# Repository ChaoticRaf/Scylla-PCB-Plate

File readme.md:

# Fork of the original Scylla PCB

My goal is to adapt the pcb of the main part and the thumbclusters to use hotswap sockets. In particular I plan to use Kailh MX Hotswap sockets with salvaged MX Blues. They are not clear so the per key RGB wont work, but I will keep the option open as I go forward.
I will try to post updates and pictures of the progress once I order the parts.

# Scylla PCB - plate

Flexible PCB made for the Scylla.

With per-key RGB.

This repository contains all files necessary to order a PCB.

If you want to modify the design files, the Kicad sources are included.
<!-- If you just want to order the PCBs, check out the Release section which contain the gerber files. -->

## How to order
Order with a 0.6mm or 0.8mm PCB thickness

# Support the original creator on Patreon
If you like the keyboard, please consider helping bastardkb on Patreon: https://www.patreon.com/bastardkb

## License
Licensed under CC BY-NC-SA 4.0
Copyright Quentin Lebastard 2021

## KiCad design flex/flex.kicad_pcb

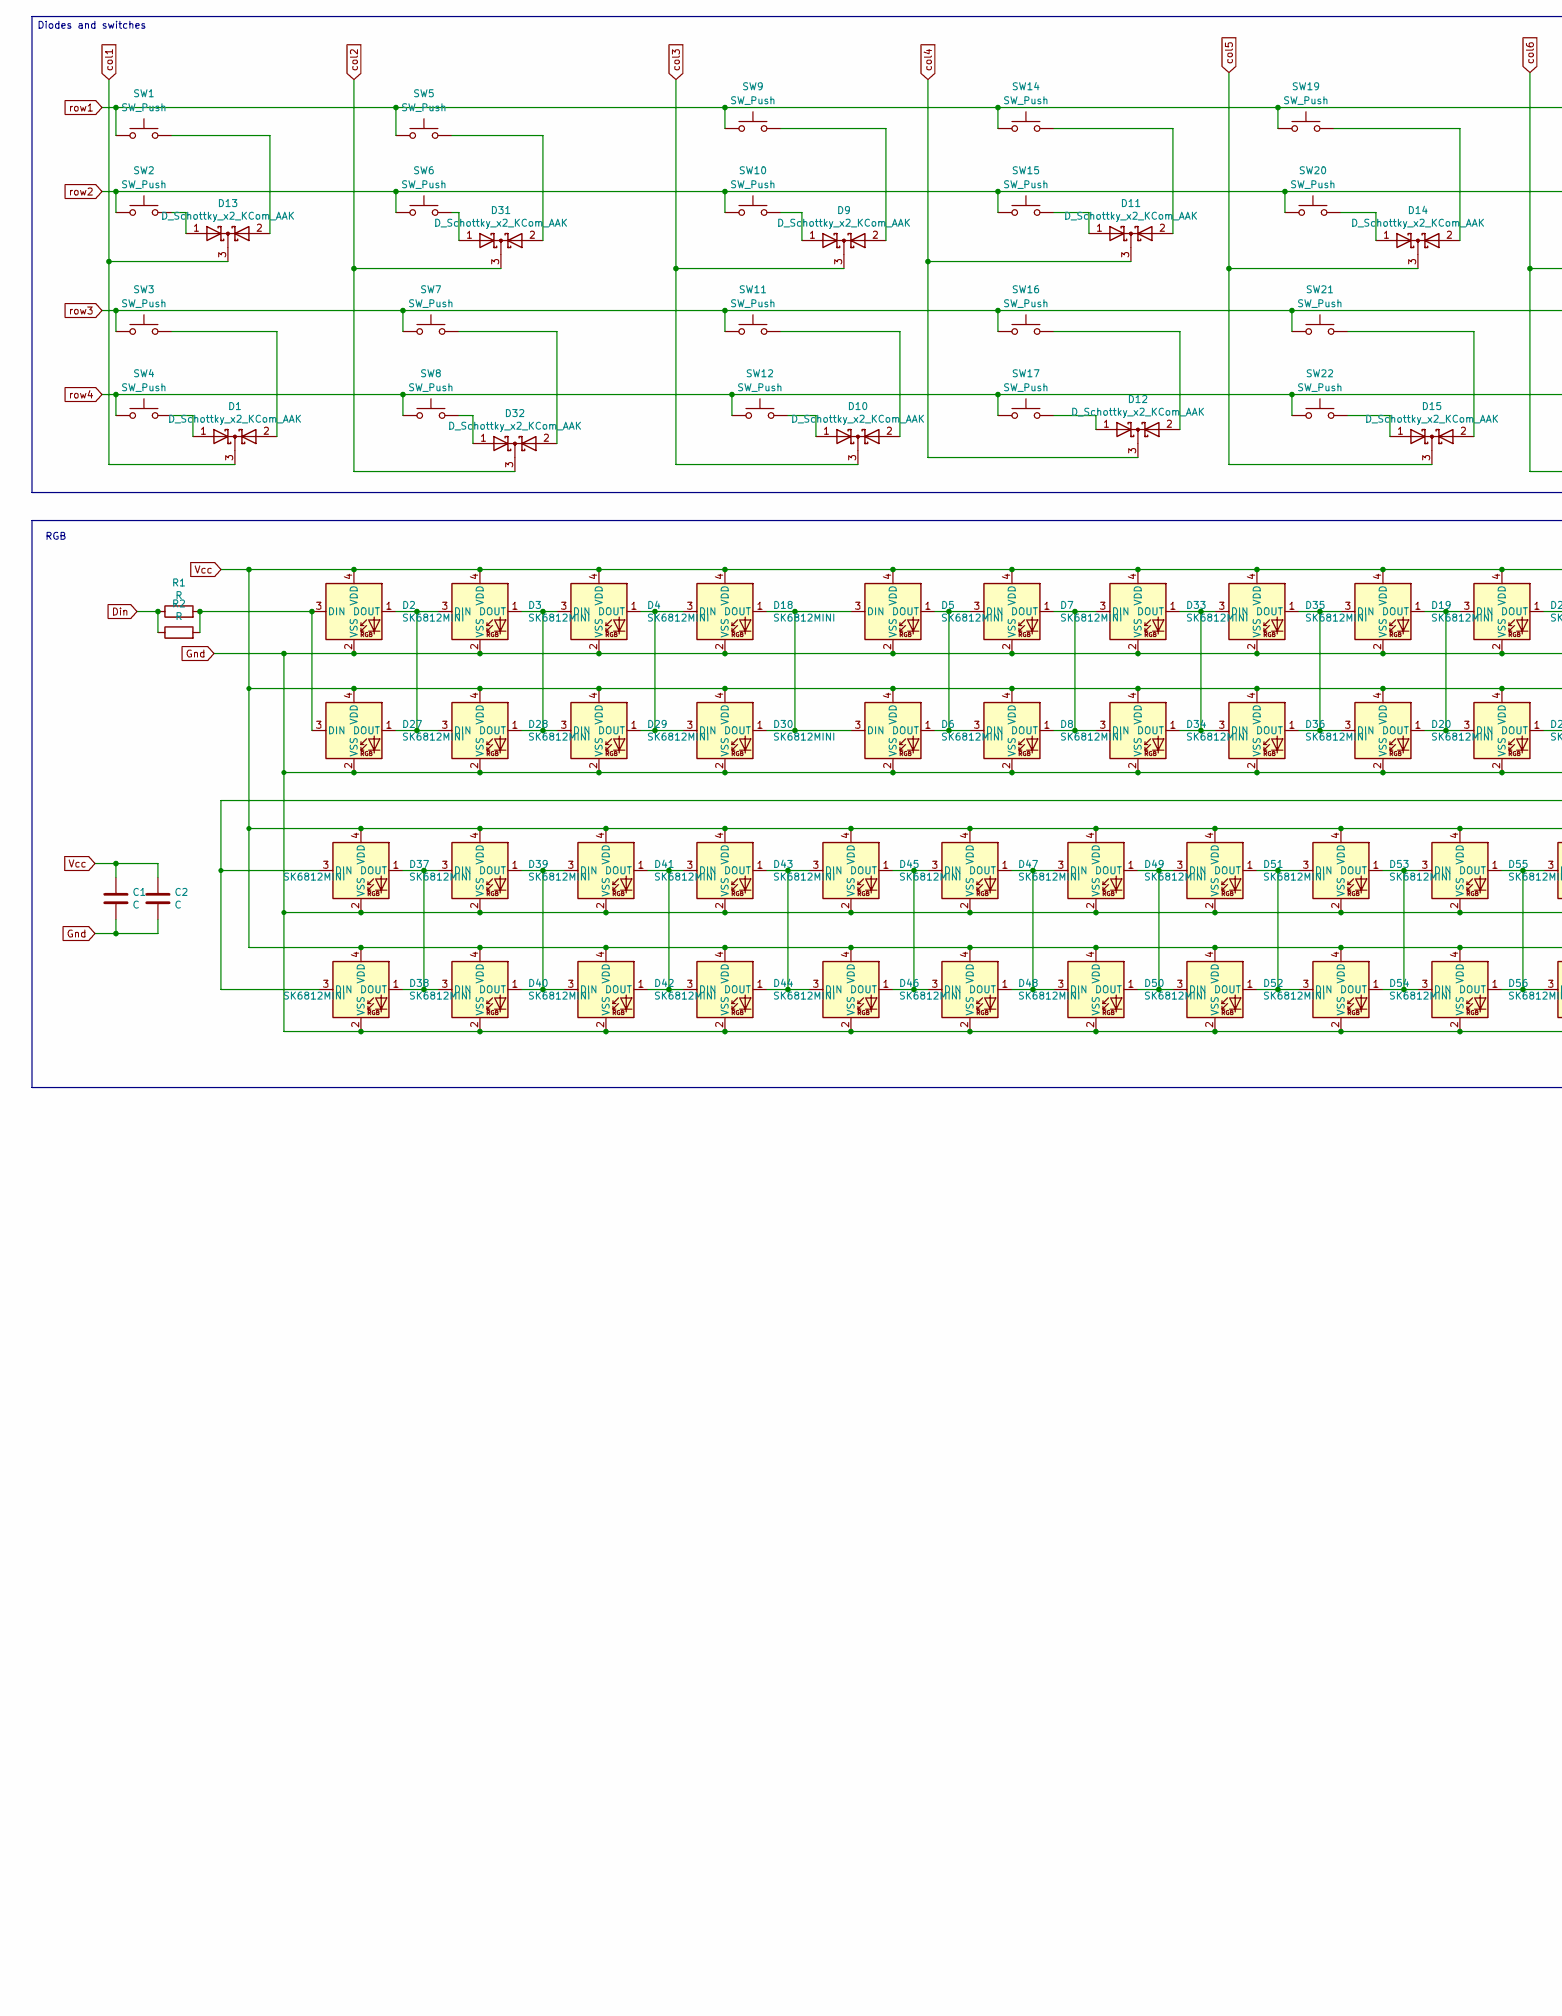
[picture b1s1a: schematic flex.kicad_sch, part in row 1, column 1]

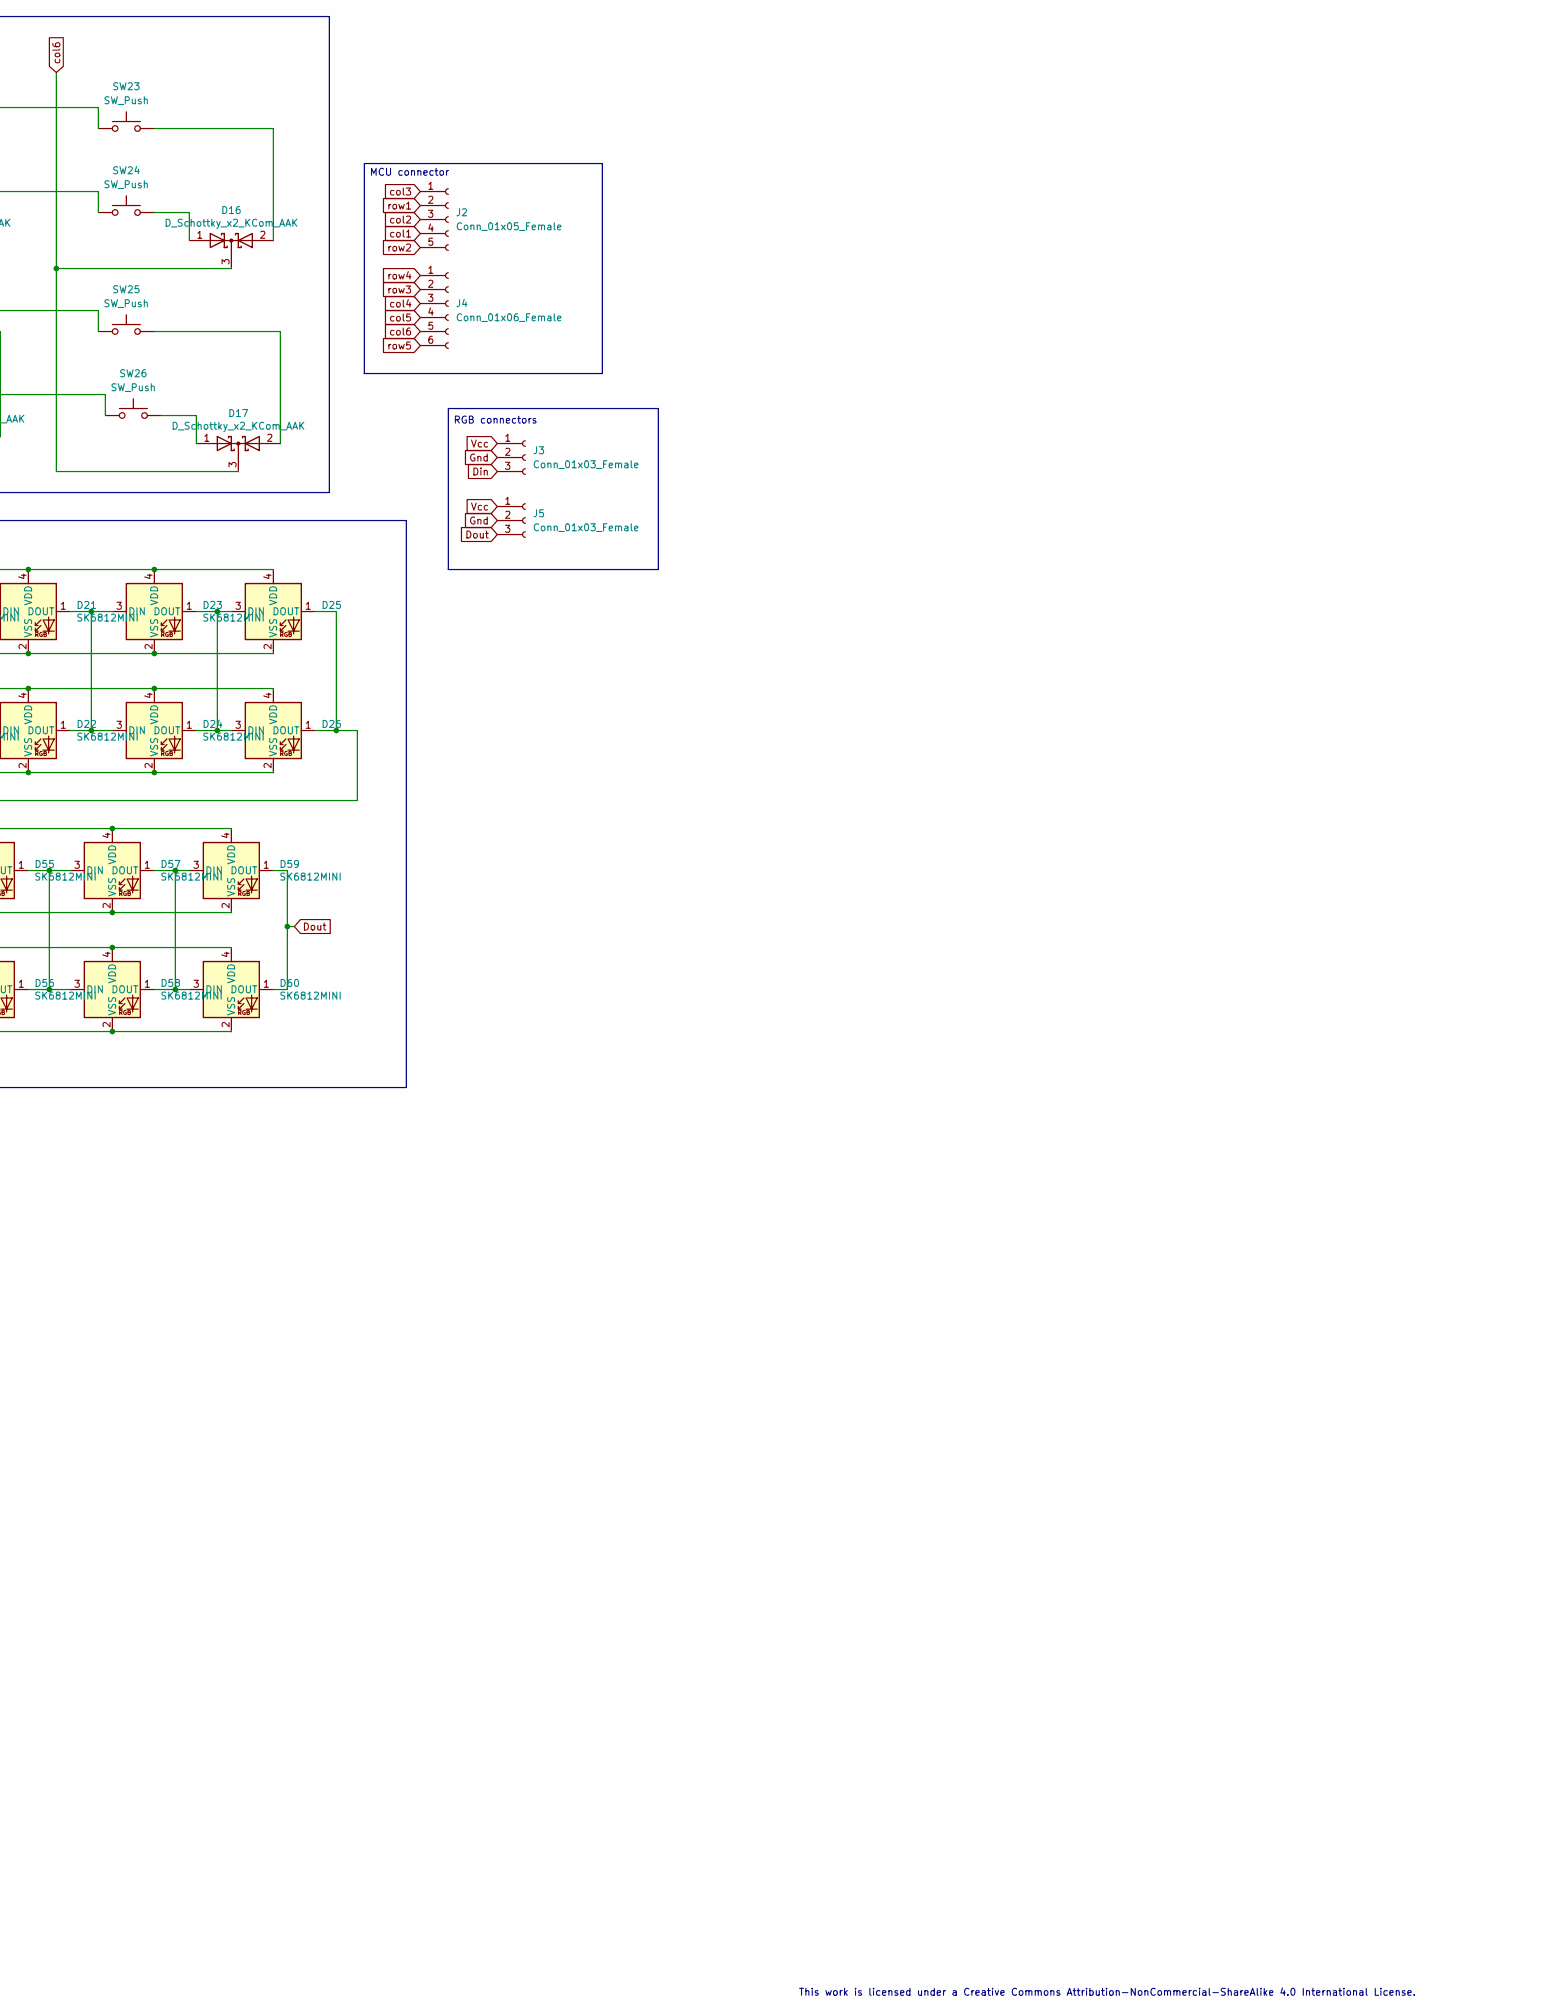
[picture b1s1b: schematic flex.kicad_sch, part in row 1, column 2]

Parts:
C1, C2: C; C_1206_3216Metric_Pad1.42x1.75mm_HandSolder
D1, D9, D10, D11, D12, D13, D14, D15, D16, D17, D31, D32: D_Schottky_x2_KCom_AAK; TSOT-23_HandSoldering
D2, D3, D4, D5, D7, D18, D19, D21, D23, D25, D33, D35, D37, D39, D41, D43, D45, D47, D49, D51, D53, D55, D57, D59: SK6812MINI; YS-SK6812MINI-E_REVERSE
D6, D8, D20, D22, D24, D26, D27, D28, D29, D30, D34, D36, D38, D40, D42, D44, D46, D48, D50, D52, D54, D56, D58, D60: SK6812MINI; YS-SK6812MINI-E_REVERSE_NO_EDGECUT
J2: Conn_01x05_Female; PinHeader_1x05_P2.54mm_Vertical
J3, J5: Conn_01x03_Female; PinHeader_1x03_P2.54mm_Vertical
J4: Conn_01x06_Female; PinHeader_1x06_P2.54mm_Vertical
R1, R2: R; R_1206_3216Metric_Pad1.42x1.75mm_HandSolder
SW1, SW2, SW3, SW4, SW5, SW6, SW7, SW8, SW9, SW10, SW11, SW12, SW14, SW15, SW16, SW17, SW19, SW20, SW21, SW22, SW23, SW24, SW25, SW26: SW_Push; Kailh_socket_MX_flippable

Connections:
Din: J3.3, R1.1, R2.1
Dout: D59.1 (DOUT), D60.1 (DOUT), J5.3
Gnd: C1.2, C2.2, D2.2 (VSS), D3.2 (VSS), D4.2 (VSS), D5.2 (VSS), D6.2 (VSS), D7.2 (VSS), D8.2 (VSS), D18.2 (VSS), D19.2 (VSS), D20.2 (VSS), D21.2 (VSS), D22.2 (VSS), D23.2 (VSS), D24.2 (VSS), D25.2 (VSS), D26.2 (VSS), D27.2 (VSS), D28.2 (VSS), D29.2 (VSS), D30.2 (VSS), D33.2 (VSS), D34.2 (VSS), D35.2 (VSS), D36.2 (VSS), D37.2 (VSS), D38.2 (VSS), D39.2 (VSS), D40.2 (VSS), D41.2 (VSS), D42.2 (VSS), D43.2 (VSS), D44.2 (VSS), D45.2 (VSS), D46.2 (VSS), D47.2 (VSS), D48.2 (VSS), D49.2 (VSS), D50.2 (VSS), D51.2 (VSS), D52.2 (VSS), D53.2 (VSS), D54.2 (VSS), D55.2 (VSS), D56.2 (VSS), D57.2 (VSS), D58.2 (VSS), D59.2 (VSS), D60.2 (VSS), J3.2, J5.2
unnamed: D1.1 (A), SW4.2
unnamed: D1.2 (A), SW3.2
unnamed: D2.1 (DOUT), D3.3 (DIN), D27.1 (DOUT), D28.3 (DIN)
unnamed: D2.3 (DIN), D27.3 (DIN), R1.2, R2.2
unnamed: D5.1 (DOUT), D6.1 (DOUT), D7.3 (DIN), D8.3 (DIN)
unnamed: D9.1 (A), SW10.2
unnamed: D9.2 (A), SW9.2
unnamed: D10.1 (A), SW12.2
unnamed: D10.2 (A), SW11.2
unnamed: D11.1 (A), SW15.2
unnamed: D11.2 (A), SW14.2
unnamed: D12.1 (A), SW17.2
unnamed: D12.2 (A), SW16.2
unnamed: D13.1 (A), SW2.2
unnamed: D13.2 (A), SW1.2
unnamed: D14.1 (A), SW20.2
unnamed: D14.2 (A), SW19.2
unnamed: D15.1 (A), SW22.2
unnamed: D15.2 (A), SW21.2
unnamed: D16.1 (A), SW24.2
unnamed: D16.2 (A), SW23.2
unnamed: D17.1 (A), SW26.2
unnamed: D17.2 (A), SW25.2
unnamed: D5.3 (DIN), D6.3 (DIN), D18.1 (DOUT), D30.1 (DOUT)
unnamed: D4.1 (DOUT), D18.3 (DIN), D29.1 (DOUT), D30.3 (DIN)
unnamed: D19.1 (DOUT), D20.1 (DOUT), D21.3 (DIN), D22.3 (DIN)
unnamed: D19.3 (DIN), D20.3 (DIN), D35.1 (DOUT), D36.1 (DOUT)
unnamed: D21.1 (DOUT), D22.1 (DOUT), D23.3 (DIN), D24.3 (DIN)
unnamed: D23.1 (DOUT), D24.1 (DOUT), D25.3 (DIN), D26.3 (DIN)
unnamed: D25.1 (DOUT), D26.1 (DOUT), D37.3 (DIN), D38.3 (DIN)
unnamed: D3.1 (DOUT), D4.3 (DIN), D28.1 (DOUT), D29.3 (DIN)
unnamed: D31.1 (A), SW6.2
unnamed: D31.2 (A), SW5.2
unnamed: D32.1 (A), SW8.2
unnamed: D32.2 (A), SW7.2
unnamed: D33.1 (DOUT), D34.1 (DOUT), D35.3 (DIN), D36.3 (DIN)
unnamed: D7.1 (DOUT), D8.1 (DOUT), D33.3 (DIN), D34.3 (DIN)
unnamed: D37.1 (DOUT), D38.1 (DOUT), D39.3 (DIN), D40.3 (DIN)
unnamed: D39.1 (DOUT), D40.1 (DOUT), D41.3 (DIN), D42.3 (DIN)
unnamed: D41.1 (DOUT), D42.1 (DOUT), D43.3 (DIN), D44.3 (DIN)
unnamed: D43.1 (DOUT), D44.1 (DOUT), D45.3 (DIN), D46.3 (DIN)
unnamed: D45.1 (DOUT), D46.1 (DOUT), D47.3 (DIN), D48.3 (DIN)
unnamed: D47.1 (DOUT), D48.1 (DOUT), D49.3 (DIN), D50.3 (DIN)
unnamed: D49.1 (DOUT), D50.1 (DOUT), D51.3 (DIN), D52.3 (DIN)
unnamed: D51.1 (DOUT), D52.1 (DOUT), D53.3 (DIN), D54.3 (DIN)
unnamed: D53.1 (DOUT), D54.1 (DOUT), D55.3 (DIN), D56.3 (DIN)
unnamed: D55.1 (DOUT), D56.1 (DOUT), D57.3 (DIN), D58.3 (DIN)
unnamed: D57.1 (DOUT), D58.1 (DOUT), D59.3 (DIN), D60.3 (DIN)
Vcc: C1.1, C2.1, D2.4 (VDD), D3.4 (VDD), D4.4 (VDD), D5.4 (VDD), D6.4 (VDD), D7.4 (VDD), D8.4 (VDD), D18.4 (VDD), D19.4 (VDD), D20.4 (VDD), D21.4 (VDD), D22.4 (VDD), D23.4 (VDD), D24.4 (VDD), D25.4 (VDD), D26.4 (VDD), D27.4 (VDD), D28.4 (VDD), D29.4 (VDD), D30.4 (VDD), D33.4 (VDD), D34.4 (VDD), D35.4 (VDD), D36.4 (VDD), D37.4 (VDD), D38.4 (VDD), D39.4 (VDD), D40.4 (VDD), D41.4 (VDD), D42.4 (VDD), D43.4 (VDD), D44.4 (VDD), D45.4 (VDD), D46.4 (VDD), D47.4 (VDD), D48.4 (VDD), D49.4 (VDD), D50.4 (VDD), D51.4 (VDD), D52.4 (VDD), D53.4 (VDD), D54.4 (VDD), D55.4 (VDD), D56.4 (VDD), D57.4 (VDD), D58.4 (VDD), D59.4 (VDD), D60.4 (VDD), J3.1, J5.1
col1: D1.3 (K), D13.3 (K), J2.4
col2: D31.3 (K), D32.3 (K), J2.3
col3: D9.3 (K), D10.3 (K), J2.1
col4: D11.3 (K), D12.3 (K), J4.3
col5: D14.3 (K), D15.3 (K), J4.4
col6: D16.3 (K), D17.3 (K), J4.5
row1: J2.2, SW1.1, SW5.1, SW9.1, SW14.1, SW19.1, SW23.1
row2: J2.5, SW2.1, SW6.1, SW10.1, SW15.1, SW20.1, SW24.1
row3: J4.2, SW3.1, SW7.1, SW11.1, SW16.1, SW21.1, SW25.1
row4: J4.1, SW4.1, SW8.1, SW12.1, SW17.1, SW22.1, SW26.1
row5: J4.6

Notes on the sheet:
Diodes and switches
RGB
MCU connector
This work is licensed under a Creative Commons Attribution-NonCommercial-ShareAlike 4.0 International License.
RGB connectors

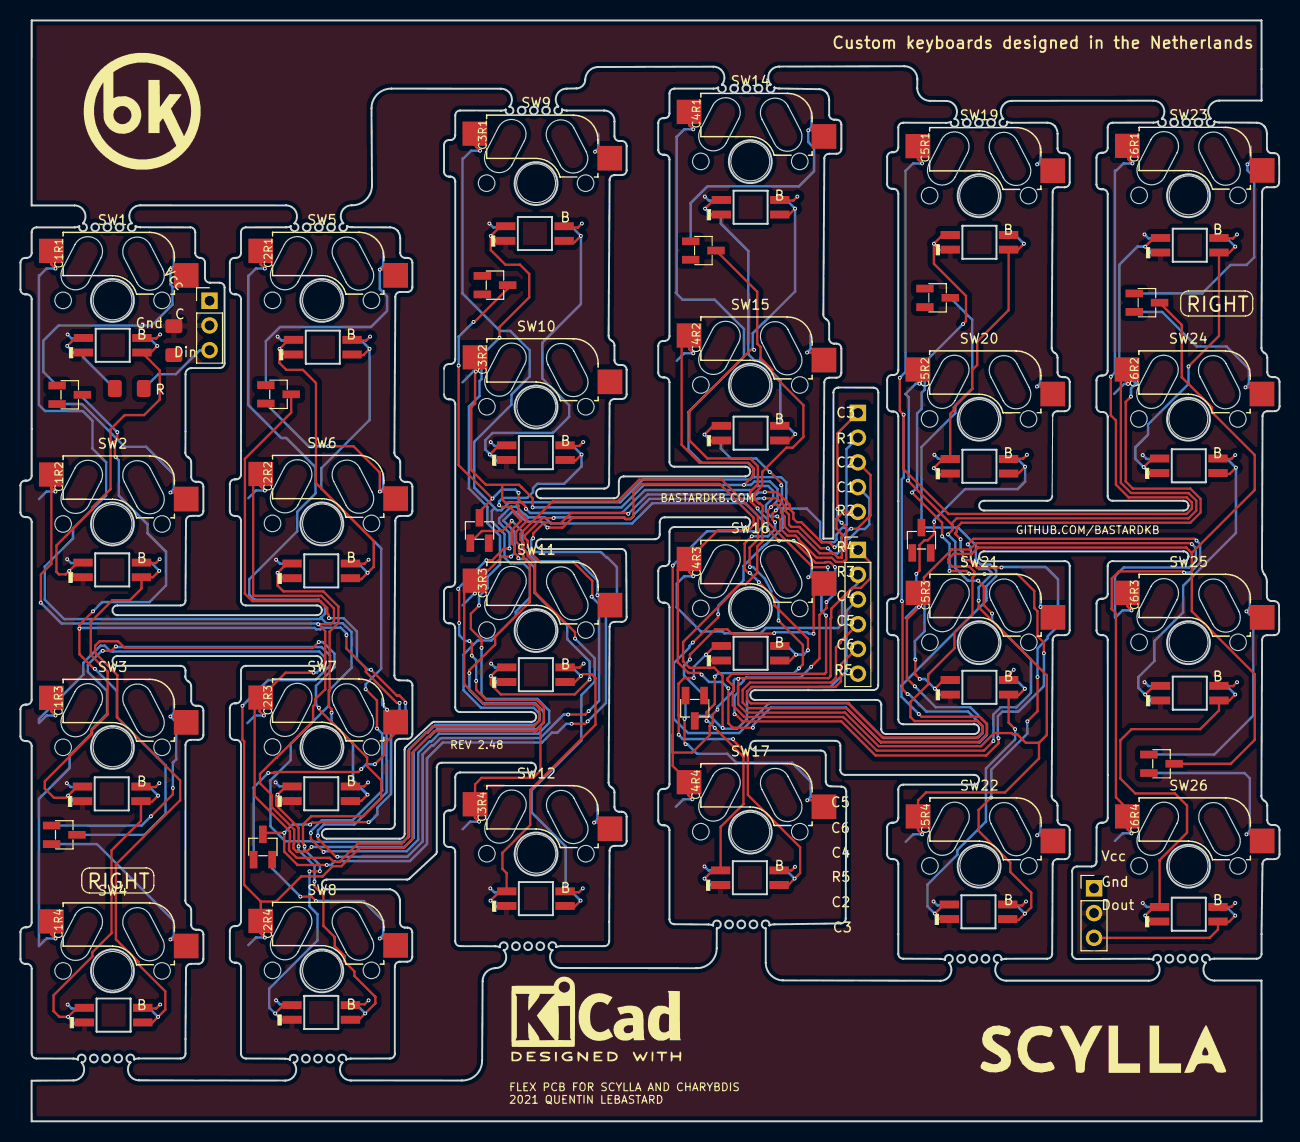
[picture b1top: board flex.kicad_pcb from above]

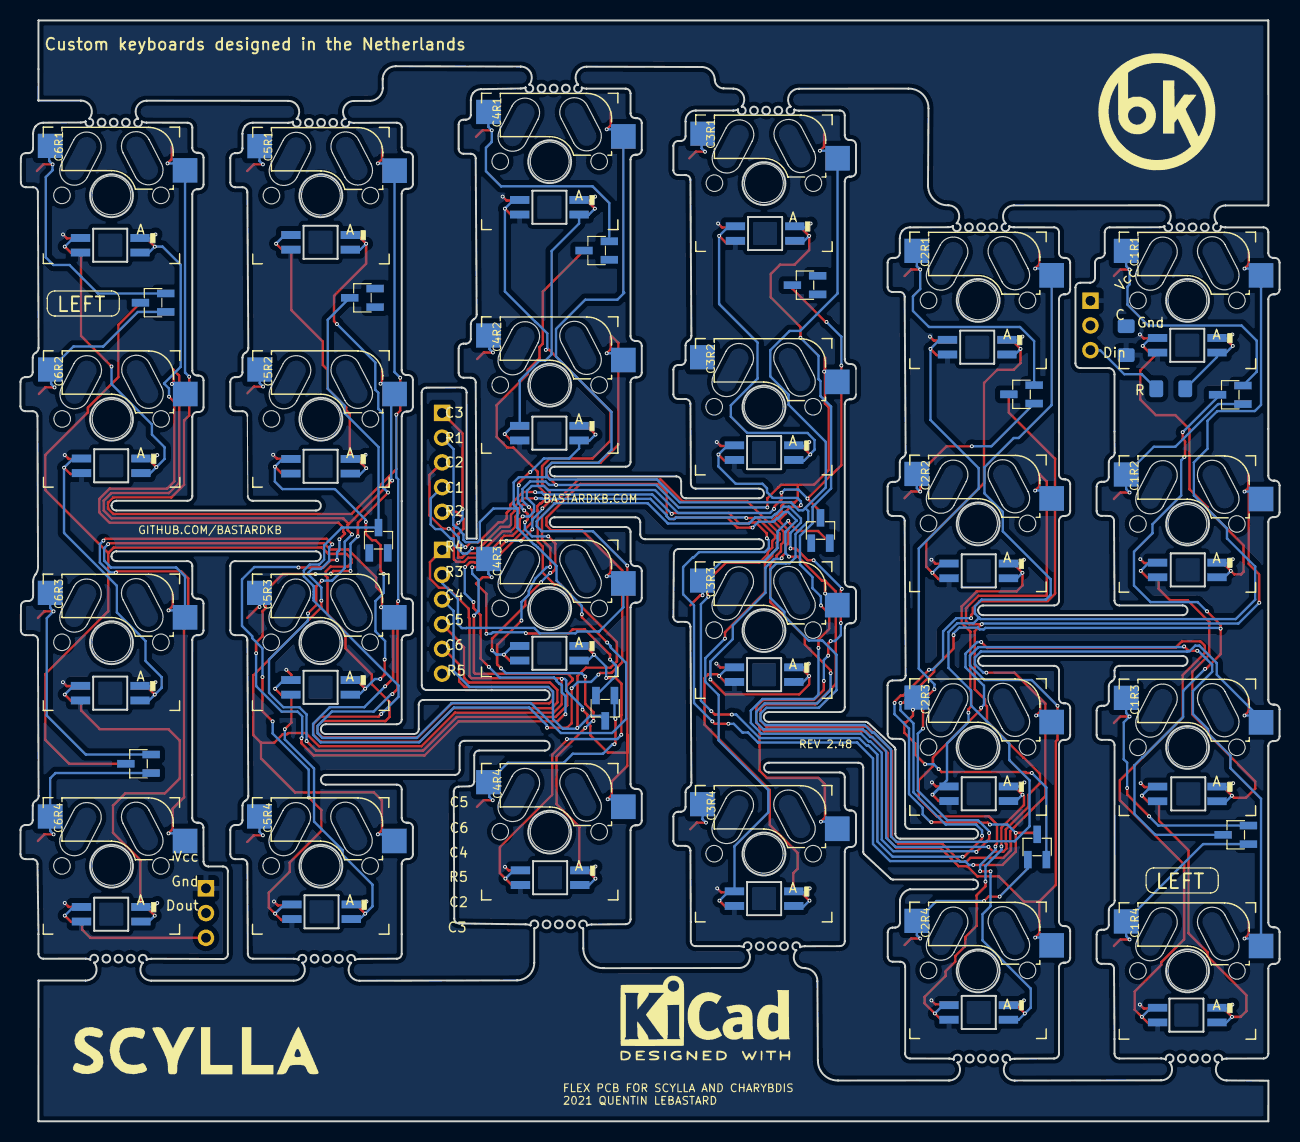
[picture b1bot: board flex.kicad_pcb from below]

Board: 2 copper layers, 129.3 x 113.0 mm, 92 parts (50 on the bottom side), 62 nets.

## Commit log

2023-09-16 added hotswap footprint
    currently incomplete, imported daprice's Kailh footprint and modified it to fit flip it horizontally.
    Will continue some other time.
    Major kudos to bastardkb for already making the pcb flippable!
2023-09-30 fixed outline, started routing
    Softly confused bout the doubled diode footprint. Assume that they are for flexibility. Will probably do something about it.
2023-10-02 Wired most of it
    Diodes and cleanup left
2023-10-05 Routed diodes
    now only the planes need to connect

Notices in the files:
flex/flex.kicad_sch:
Copyright Quentin Lebastard 2022
